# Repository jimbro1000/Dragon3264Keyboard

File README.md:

# Reproduction Keyboard for Dragon 32 and 64 #

This project provides the designs for a reproduction keyboard
to fit the Dragon 32 and 64 home computers. The design uses modern
Cherry MX compatible switch mounts to facilitate the easy use of
readily available keycaps.

## Status ##

The first draft of the board has been produced for testing

The good bits:
* The layout fits the keyboard aperture in the case
* The height of the board appears to be correct at 20mm higher than
the original

The bad bits:
* The first draft is 5.3mm too wide - but the layout is all referenced
from the top left of the board and this is correct. The only fault is
the right hand edge and the right hand mounting point

## Changes to the original ##

The keyboard matrix includes a diode alongside each switch to 
remove ghosting issues. This isn't strictly necessary but if
you want to utilise a cheap MCU like the atmega32u4 to convert
the keyboard to USB HID, you are going to need those diodes.

If you decide not to use them you will need to bridge the pads
for each diode position, this then replicates the original
keyboard matrix

### Using a microcontroller for USB ###

The project includes design files for use with the "Keyboard
Firmware Builder" website - this generates a binary file to
program a microcontroller. The design expects the rows to be
wired to the "Bx" pins and the columns to be wired to the
"Dx" pins.

The Firmware Builder website can be found here:
[Keyboard Firmware Builder link](https://builder.mrkeebs.com/)

### Extra keys ###

The original keyboard utilises an 8u wide spacebar but these
are more just a bit tricky to find in modern fittings, the next
best alternative is a 6u wide spacebar which leaves gaps for
two more keys, wiring the keyboard to accept extra keys is
simple enough and the original matrix has space for four more
keys. The original ROMs do not include scanning for those extra
unused keys so they won't do anything without modifications to
the ROM coding. For emulation purposes it is trivial to map the
extra keys to be useful (I suggest using them as modifiers to
really expand the range of keypresses or macros that can be
operated).

The layout of the keyboard can be quickly prototyped using
another online tool called the "Keyboard Layout Editor", you
can access it here: [Keyboard Layout Editor link](http://www.keyboard-layout-editor.com/?fbclid=IwAR0KAMezcl8_ZXLS8Ygmnt5tV90nPUaG68bI-OjukuRIi-xNhSF8OInGqlg##@@_x:0.5&c=%231c1a1a&t=%23e8e8c8&p=R1&sm=cherry&sb=cherry&st=MX1A-G1xx&a:5&fa@:4&:6%3B%3B&=!%0A1&=%22%0A2&=%23%0A3&=$%0A4&=%25%0A5&=%2F&%0A6&='%0A7&=(%0A8&=)%0A9&=%0A0&=*%0A%2F:&=%2F=%0A-&_a:7&fa@:2%3B%3B&=BREAK%3B&@_fa@:6%3B%3B&=%E2%86%91&_fa@:8%3B%3B&=Q&=W&=E&=R&=T&=Y&=U&=I&=O&=P&=%2F@&_fa@:6%3B%3B&=%E2%86%90&=%E2%86%92%3B&@_x:0.25%3B&=%E2%86%93&_fa@:8%3B%3B&=A&=S&=D&=F&=G&=H&=J&=K&=L&_a:5&fa@:4&:6%3B%3B&=+%0A%2F%3B&_a:7&w:2%3B&=ENTER&_fa@:2%3B%3B&=CLEAR%3B&@_x:0.25&fa@:4%3B&w:1.5%3B&=SHIFT&_fa@:8%3B%3B&=Z&=X&=C&=V&=B&=N&=M&_a:5&fa@:4&:6%3B%3B&=%3C%0A,&=%3E%0A.&=%3F%0A%2F%2F&_a:7&w:1.5%3B&=SHIFT%3B&@_x:2.75&w:8%3B&=)

The link includes all of the original design settings but
you can also find the settings as a config file in this
repository.

The reproduction boards I've designed have the potential to 
utilise full 8-bit character set codes (through external
character generator roms and additional control lines to
the VDG), where this is done it would be necessary to use
the modifier keys to access the additional characters in
much the same way as the petscii set on vintage Commodore
computers.

## Keycaps ##

By using standard MX switches the range of key caps readily
available is immense. Brand new ready made sets are cheap
enough but keep in mind that the position of some characters
on the Dragon keyboard is non-standard (such as brackets 
appearing on the 8 and 9 keys instead of 9 and 0). You also have
a small problem with the break and clear keys as these are not
standard (yes there is a "pause break" that comes close).

Most key cap sets are also profiled differently for each row
of the keyboard, it isn't a particular problem but some keys
are in very different positions - such as the arrow keys so
the profile won't look or feel right for those keys compared
to others on the same row.

If however you are getting your keycaps fabricated there are
options to have the same profile for all of the keys **and**
have the right symbols on each key.

## Projection ##

The overall projection height (from pcb to the top of the key)
on the original keyboard is nearly 2cm more than you get with
modern keys and keycaps. If you put those in a stock case the
keys will actually be below the level of the keyboard surround.

Overcoming the difference in height needs the pcb to sit higher,
the simplest option (at the moment) is to use two layers of
boards. The first sits at the normal height and uses the original
mounting points. The second board is mounted to the first using
spacers (the pcb design includes holes for M5 sized spacers to be
mounted already).

To make the keyboard really robust it should also have a
stabilising frame above the PCB, this clips all of the switches
together into a single unit, in a similar way to the original
hi-tek switches.

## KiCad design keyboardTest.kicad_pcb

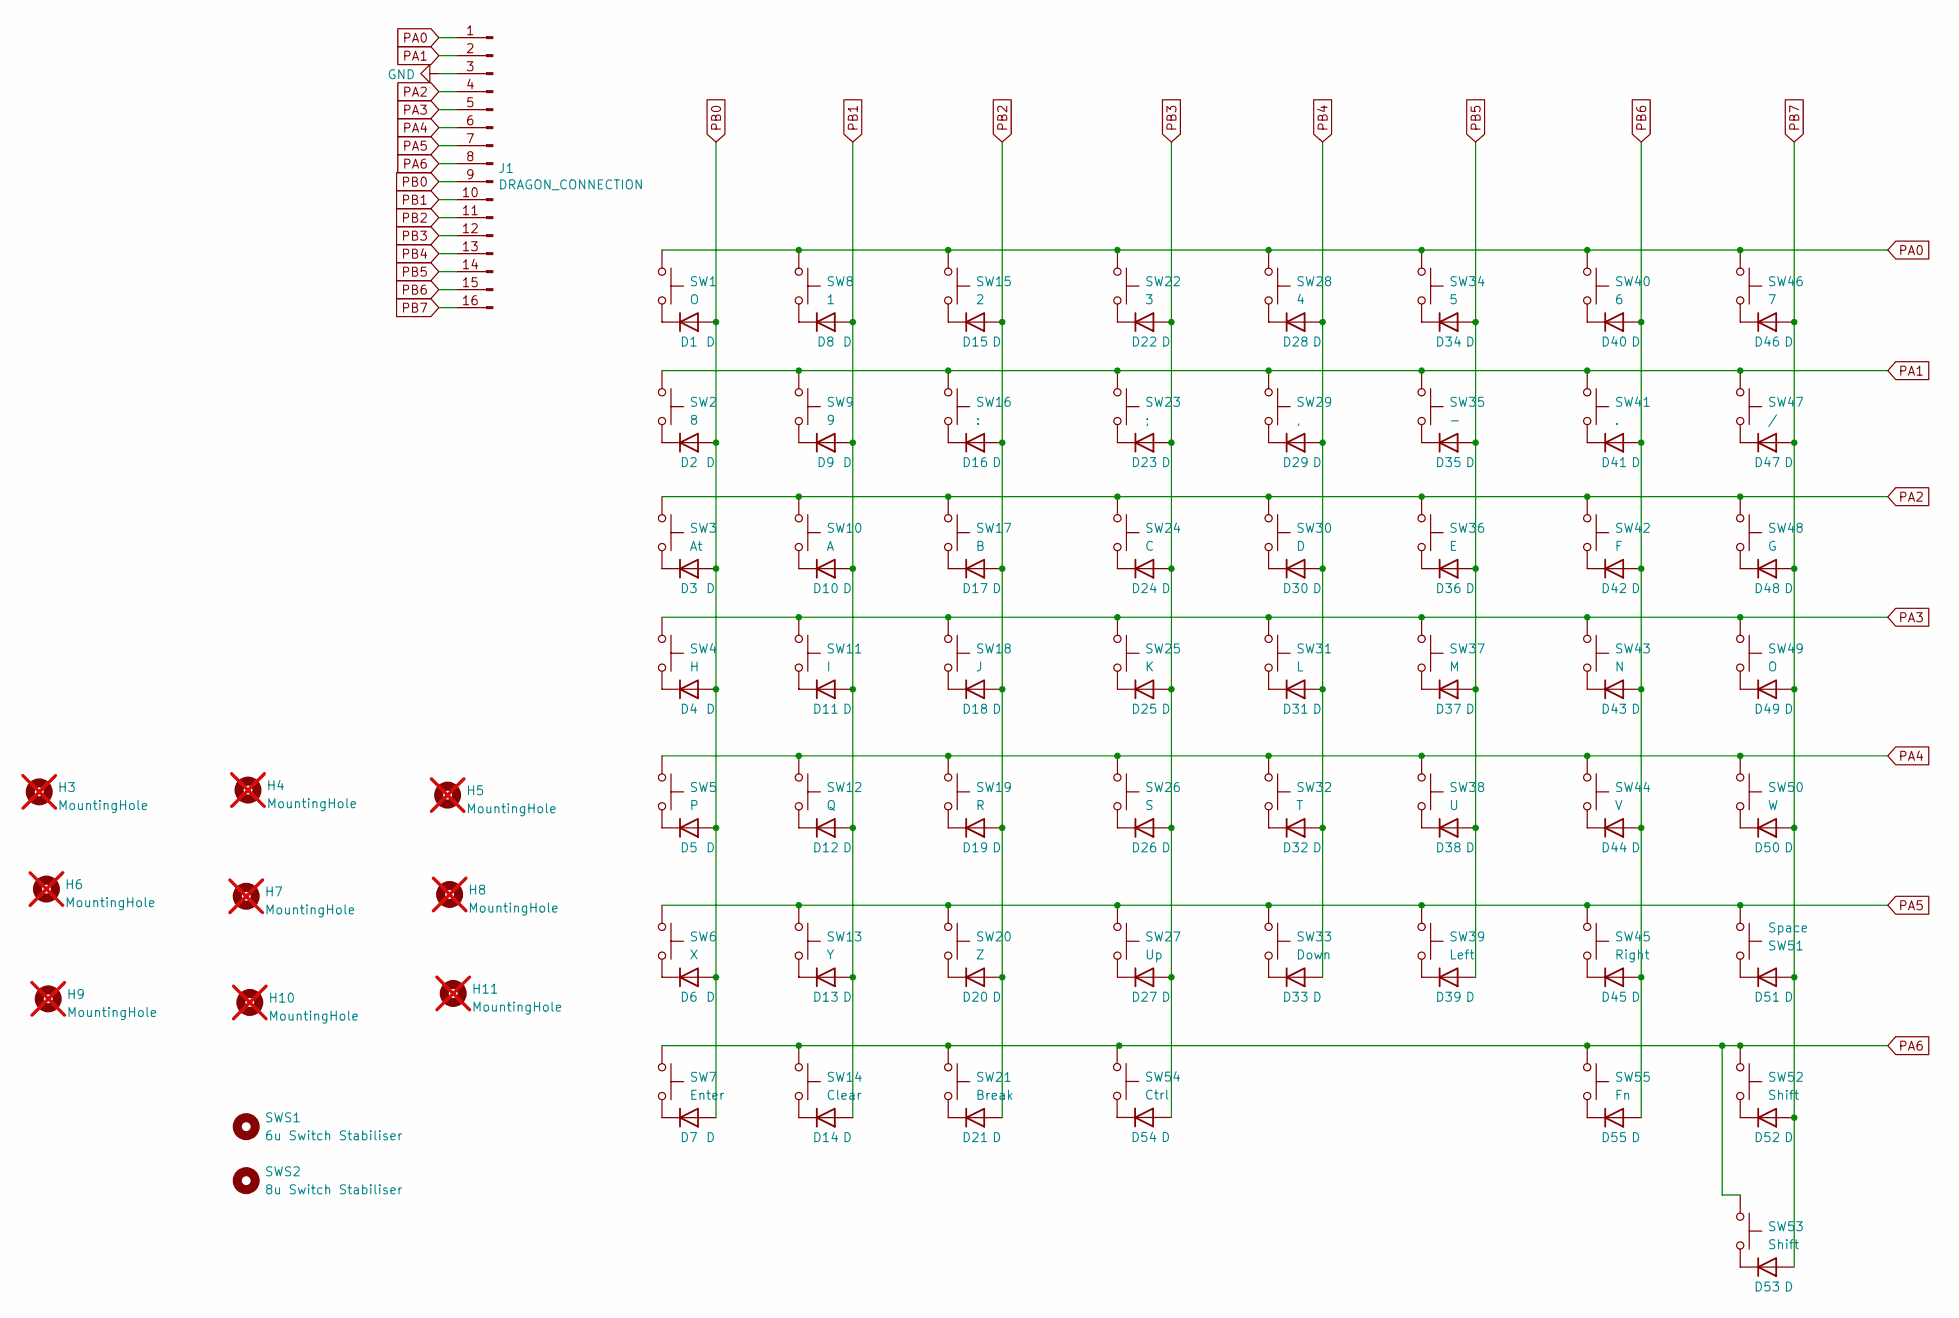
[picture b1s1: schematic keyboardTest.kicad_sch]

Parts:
D1, D2, D3, D4, D5, D6, D7, D8, D9, D10, D11, D12, D13, D14, D15, D16, D17, D18, D19, D20, D21, D22, D23, D24, D25, D26, D27, D28, D29, D30, D31, D32, D33, D34, D35, D36, D37, D38, D39, D40, D41, D42, D43, D44, D45, D46, D47, D48, D49, D50, D51, D52, D53, D54, D55: D; D_0805_2012Metric
H3, H4, H5, H6, H7, H8, H9, H10, H11: MountingHole; MountingHole_3.2mm_M3; not fitted
J1: DRAGON_CONNECTION; PinHeader_1x16_P2.54mm_Horizontal
SW1, SW49: O; SW_Cherry_MX_1.00u_PCB
SW2: 8; SW_Cherry_MX_1.00u_PCB
SW3: At; SW_Cherry_MX_1.00u_PCB
SW4: H; SW_Cherry_MX_1.00u_PCB
SW5: P; SW_Cherry_MX_1.00u_PCB
SW6: X; SW_Cherry_MX_1.00u_PCB
SW7: Enter; SW_Cherry_MX_2.00u_PCB
SW8: 1; SW_Cherry_MX_1.00u_PCB
SW9: 9; SW_Cherry_MX_1.00u_PCB
SW10: A; SW_Cherry_MX_1.00u_PCB
SW11: I; SW_Cherry_MX_1.00u_PCB
SW12: Q; SW_Cherry_MX_1.00u_PCB
SW13: Y; SW_Cherry_MX_1.00u_PCB
SW14: Clear; SW_Cherry_MX_1.00u_PCB
SW15: 2; SW_Cherry_MX_1.00u_PCB
SW16: :; SW_Cherry_MX_1.00u_PCB
SW17: B; SW_Cherry_MX_1.00u_PCB
SW18: J; SW_Cherry_MX_1.00u_PCB
SW19: R; SW_Cherry_MX_1.00u_PCB
SW20: Z; SW_Cherry_MX_1.00u_PCB
SW21: Break; SW_Cherry_MX_1.00u_PCB
SW22: 3; SW_Cherry_MX_1.00u_PCB
SW23: ;; SW_Cherry_MX_1.00u_PCB
SW24: C; SW_Cherry_MX_1.00u_PCB
SW25: K; SW_Cherry_MX_1.00u_PCB
SW26: S; SW_Cherry_MX_1.00u_PCB
SW27: Up; SW_Cherry_MX_1.00u_PCB
SW28: 4; SW_Cherry_MX_1.00u_PCB
SW29: ,; SW_Cherry_MX_1.00u_PCB
SW30: D; SW_Cherry_MX_1.00u_PCB
SW31: L; SW_Cherry_MX_1.00u_PCB
SW32: T; SW_Cherry_MX_1.00u_PCB
SW33: Down; SW_Cherry_MX_1.00u_PCB
SW34: 5; SW_Cherry_MX_1.00u_PCB
SW35: -; SW_Cherry_MX_1.00u_PCB
SW36: E; SW_Cherry_MX_1.00u_PCB
SW37: M; SW_Cherry_MX_1.00u_PCB
SW38: U; SW_Cherry_MX_1.00u_PCB
SW39: Left; SW_Cherry_MX_1.00u_PCB
SW40: 6; SW_Cherry_MX_1.00u_PCB
SW41: .; SW_Cherry_MX_1.00u_PCB
SW42: F; SW_Cherry_MX_1.00u_PCB
SW43: N; SW_Cherry_MX_1.00u_PCB
SW44: V; SW_Cherry_MX_1.00u_PCB
SW45: Right; SW_Cherry_MX_1.00u_PCB
SW46: 7; SW_Cherry_MX_1.00u_PCB
SW47: /; SW_Cherry_MX_1.00u_PCB
SW48: G; SW_Cherry_MX_1.00u_PCB
SW50: W; SW_Cherry_MX_1.00u_PCB
SW51: Space; SW_Cherry_MX_PCB_6.00u
SW52, SW53: Shift; SW_Cherry_MX_1.50u_PCB
SW54: Ctrl; SW_Cherry_MX_1.00u_PCB
SW55: Fn; SW_Cherry_MX_1.00u_PCB
SWS1: 6u Switch Stabiliser; Stabilizer_Cherry_MX_6.00u
SWS2: 8u Switch Stabiliser; Stabilizer_Cherry_MX_8.00u

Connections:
GND: J1.3
unnamed: D1.1 (K), SW1.2
unnamed: D2.1 (K), SW2.2
unnamed: D3.1 (K), SW3.2
unnamed: D4.1 (K), SW4.2
unnamed: D5.1 (K), SW5.2
unnamed: D6.1 (K), SW6.2
unnamed: D7.1 (K), SW7.2
unnamed: D8.1 (K), SW8.2
unnamed: D9.1 (K), SW9.2
unnamed: D10.1 (K), SW10.2
unnamed: D11.1 (K), SW11.2
unnamed: D12.1 (K), SW12.2
unnamed: D13.1 (K), SW13.2
unnamed: D14.1 (K), SW14.2
unnamed: D15.1 (K), SW15.2
unnamed: D16.1 (K), SW16.2
unnamed: D17.1 (K), SW17.2
unnamed: D18.1 (K), SW18.2
unnamed: D19.1 (K), SW19.2
unnamed: D20.1 (K), SW20.2
unnamed: D21.1 (K), SW21.2
unnamed: D22.1 (K), SW22.2
unnamed: D23.1 (K), SW23.2
unnamed: D24.1 (K), SW24.2
unnamed: D25.1 (K), SW25.2
unnamed: D26.1 (K), SW26.2
unnamed: D27.1 (K), SW27.2
unnamed: D28.1 (K), SW28.2
unnamed: D29.1 (K), SW29.2
unnamed: D30.1 (K), SW30.2
unnamed: D31.1 (K), SW31.2
unnamed: D32.1 (K), SW32.2
unnamed: D33.1 (K), SW33.2
unnamed: D34.1 (K), SW34.2
unnamed: D35.1 (K), SW35.2
unnamed: D36.1 (K), SW36.2
unnamed: D37.1 (K), SW37.2
unnamed: D38.1 (K), SW38.2
unnamed: D39.1 (K), SW39.2
unnamed: D40.1 (K), SW40.2
unnamed: D41.1 (K), SW41.2
unnamed: D42.1 (K), SW42.2
unnamed: D43.1 (K), SW43.2
unnamed: D44.1 (K), SW44.2
unnamed: D45.1 (K), SW45.2
unnamed: D46.1 (K), SW46.2
unnamed: D47.1 (K), SW47.2
unnamed: D48.1 (K), SW48.2
unnamed: D49.1 (K), SW49.2
unnamed: D50.1 (K), SW50.2
unnamed: D51.1 (K), SW51.1
unnamed: D52.1 (K), SW52.2
unnamed: D53.1 (K), SW53.2
unnamed: D54.1 (K), SW54.2
unnamed: D55.1 (K), SW55.2
PA0: J1.1, SW1.1, SW8.1, SW15.1, SW22.1, SW28.1, SW34.1, SW40.1, SW46.1
PA1: J1.2, SW2.1, SW9.1, SW16.1, SW23.1, SW29.1, SW35.1, SW41.1, SW47.1
PA2: J1.4, SW3.1, SW10.1, SW17.1, SW24.1, SW30.1, SW36.1, SW42.1, SW48.1
PA3: J1.5, SW4.1, SW11.1, SW18.1, SW25.1, SW31.1, SW37.1, SW43.1, SW49.1
PA4: J1.6, SW5.1, SW12.1, SW19.1, SW26.1, SW32.1, SW38.1, SW44.1, SW50.1
PA5: J1.7, SW6.1, SW13.1, SW20.1, SW27.1, SW33.1, SW39.1, SW45.1, SW51.2
PA6: J1.8, SW7.1, SW14.1, SW21.1, SW52.1, SW53.1, SW54.1, SW55.1
PB0: D1.2 (A), D2.2 (A), D3.2 (A), D4.2 (A), D5.2 (A), D6.2 (A), D7.2 (A), J1.9
PB1: D8.2 (A), D9.2 (A), D10.2 (A), D11.2 (A), D12.2 (A), D13.2 (A), D14.2 (A), J1.10
PB2: D15.2 (A), D16.2 (A), D17.2 (A), D18.2 (A), D19.2 (A), D20.2 (A), D21.2 (A), J1.11
PB3: D22.2 (A), D23.2 (A), D24.2 (A), D25.2 (A), D26.2 (A), D27.2 (A), D54.2 (A), J1.12
PB4: D28.2 (A), D29.2 (A), D30.2 (A), D31.2 (A), D32.2 (A), D33.2 (A), J1.13
PB5: D34.2 (A), D35.2 (A), D36.2 (A), D37.2 (A), D38.2 (A), D39.2 (A), J1.14
PB6: D40.2 (A), D41.2 (A), D42.2 (A), D43.2 (A), D44.2 (A), D45.2 (A), D55.2 (A), J1.15
PB7: D46.2 (A), D47.2 (A), D48.2 (A), D49.2 (A), D50.2 (A), D51.2 (A), D52.2 (A), D53.2 (A), J1.16

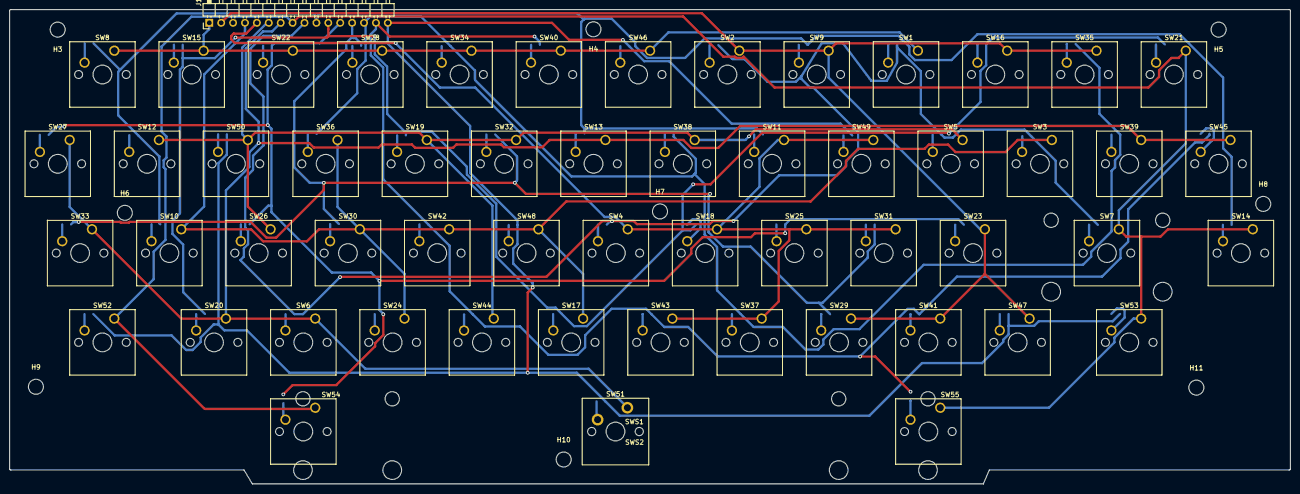
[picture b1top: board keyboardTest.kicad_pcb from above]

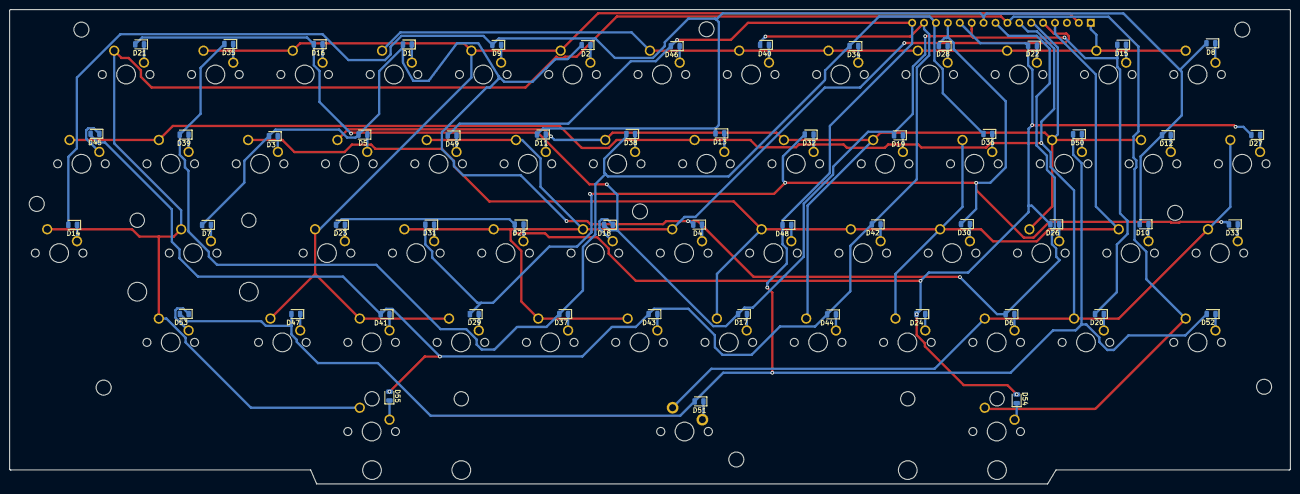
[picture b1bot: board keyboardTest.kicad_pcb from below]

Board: 2 copper layers, 273.3 x 101.2 mm, 122 parts (55 on the bottom side), 70 nets.

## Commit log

2023-06-18 update pcb render
2023-06-20 correct board dimensions
2023-06-20 rectify spacebar row
2023-06-20 add new render
2023-06-21 update pcb for spare stabiliser position
2023-06-24 add stl files for key switch plates
2023-06-24 render of switch plate
2023-06-24 add switch plate to readme
2023-07-26 revise board dimensions
2023-08-07 shrinkify board
2023-08-07 add support files for plus 2 layout
